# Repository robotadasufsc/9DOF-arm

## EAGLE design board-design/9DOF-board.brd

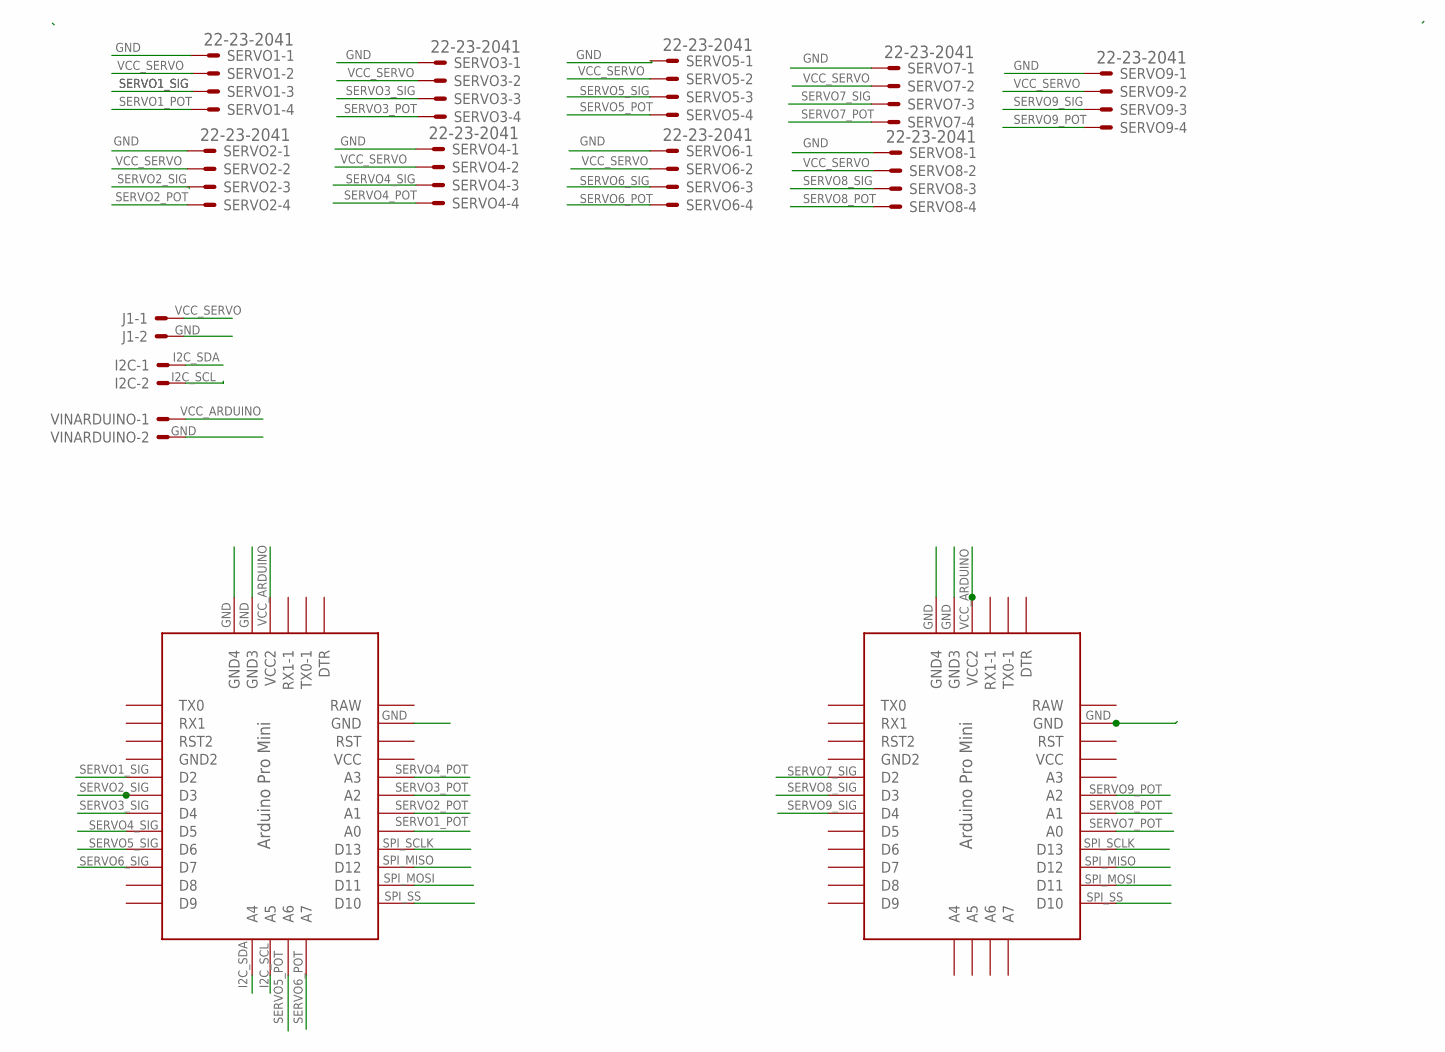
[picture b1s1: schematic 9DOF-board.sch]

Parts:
I2C: 22-23-2021
J1: 22-23-2021
SERVO1, SERVO2, SERVO3, SERVO4, SERVO5, SERVO6, SERVO7, SERVO8, SERVO9: 22-23-2041
U$1, U$2: PRO-MINI
VINARDUINO: 22-23-2021

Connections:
GND: J1.2, SERVO1.1, SERVO2.1, SERVO3.1, SERVO4.1, SERVO6.1, SERVO7.1, SERVO8.1, SERVO9.1, U$1.GND, U$1.GND2 (GND4), U$1.GND3, U$2.GND, U$2.GND2 (GND4), U$2.GND3, VINARDUINO.2
I2C_SCL: I2C.2, U$1.A5
I2C_SDA: I2C.1, U$1.A4
RAW: U$1.RAW, U$2.RAW
SERVO1_POT: SERVO1.4, U$1.A0
SERVO1_SIG: SERVO1.3, U$1.D2
SERVO2_POT: SERVO2.4, U$1.A1
SERVO2_SIG: SERVO2.3, U$1.D3
SERVO3_POT: SERVO3.4, U$1.A2
SERVO3_SIG: SERVO3.3, U$1.D4
SERVO4_POT: SERVO4.4, U$1.A3
SERVO4_SIG: SERVO4.3, U$1.D5
SERVO5_POT: SERVO5.4, U$1.A6
SERVO5_SIG: SERVO5.3, U$1.D6
SERVO6_POT: SERVO6.4, U$1.A7
SERVO6_SIG: SERVO6.3, U$1.D7
SERVO7_POT: SERVO7.4, U$2.A0
SERVO7_SIG: SERVO7.3, U$2.D2
SERVO8_POT: SERVO8.4, U$2.A1
SERVO8_SIG: SERVO8.3, U$2.D3
SERVO9_POT: SERVO9.4, U$2.A2
SERVO9_SIG: SERVO9.3, U$2.D4
SPI_MISO: U$1.D12, U$2.D12
SPI_MOSI: U$1.D11, U$2.D11
SPI_SCLK: U$1.D13, U$2.D13
SPI_SS: U$1.D10, U$2.D10
VCC_ARDUINO: U$1.VCC1 (VCC2), U$2.VCC1 (VCC2), VINARDUINO.1
VCC_SERVO: J1.1, SERVO1.2, SERVO2.2, SERVO3.2, SERVO4.2, SERVO5.2, SERVO6.2, SERVO7.2, SERVO8.2, SERVO9.2

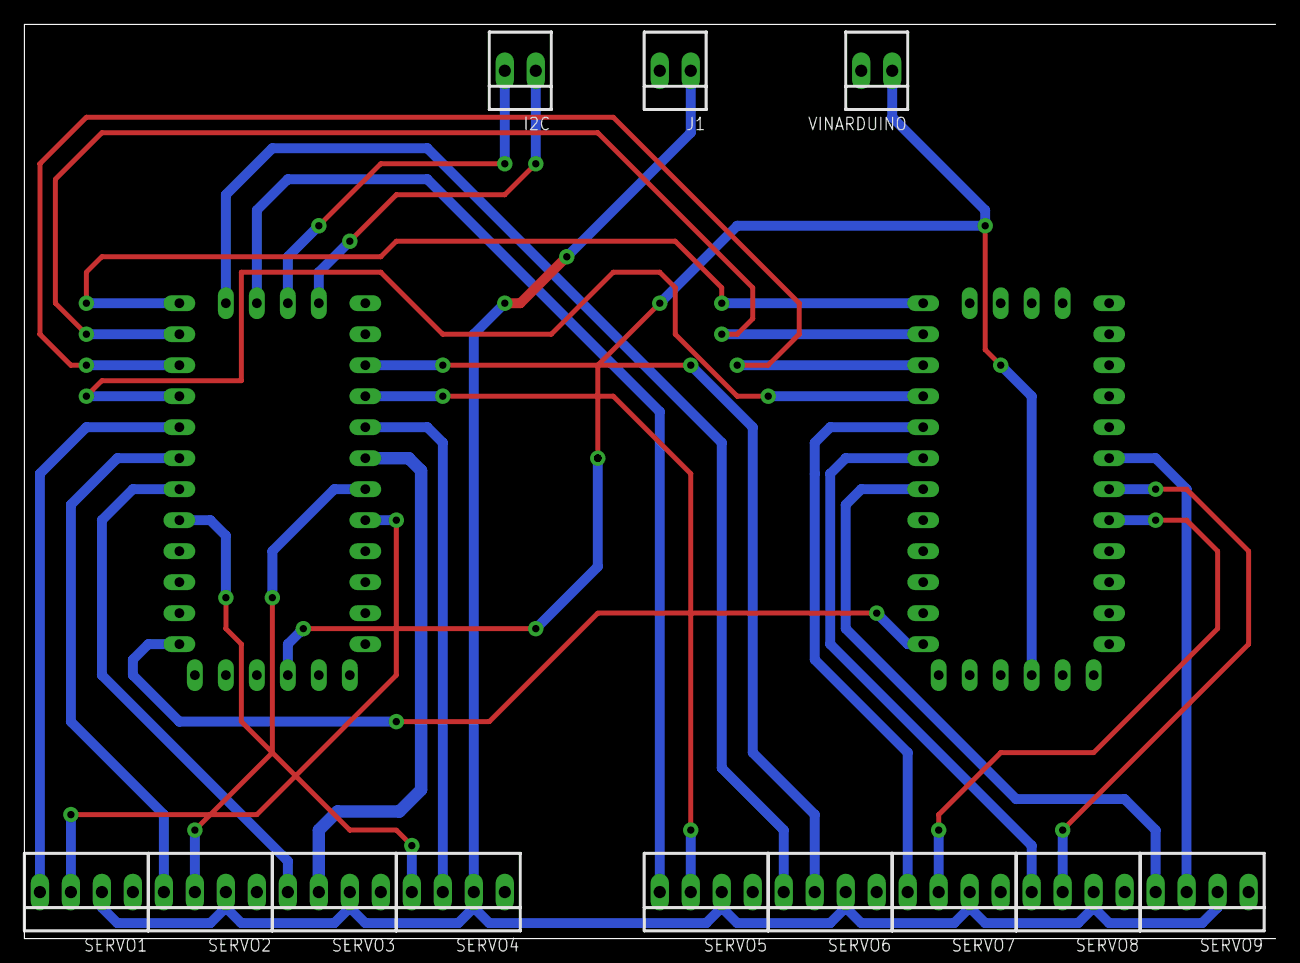
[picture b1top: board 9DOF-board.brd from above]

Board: 2 copper layers, 102.5 x 74.9 mm, 14 parts (0 on the bottom side), 28 nets.

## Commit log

2017-06-06 added eagle files
2017-06-09 updated gitignore file
2017-06-09 added arduino and connectors
2017-06-12 First connections between uC and external connectors.
2017-07-17 Add files via upload
    PCB Layout v0.1
2017-07-28 SPI connections between Arduinos done
2017-08-06 Track size increased and jumper routings optimized.
2017-08-12 changed clearance for milling machine compatibility
2017-08-14 clearance adjustment
2017-08-14 fixed clearance error
